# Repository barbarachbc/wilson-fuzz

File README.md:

# wilson-fuzz
Wilson Fuzz (a Fuzz Face clone)

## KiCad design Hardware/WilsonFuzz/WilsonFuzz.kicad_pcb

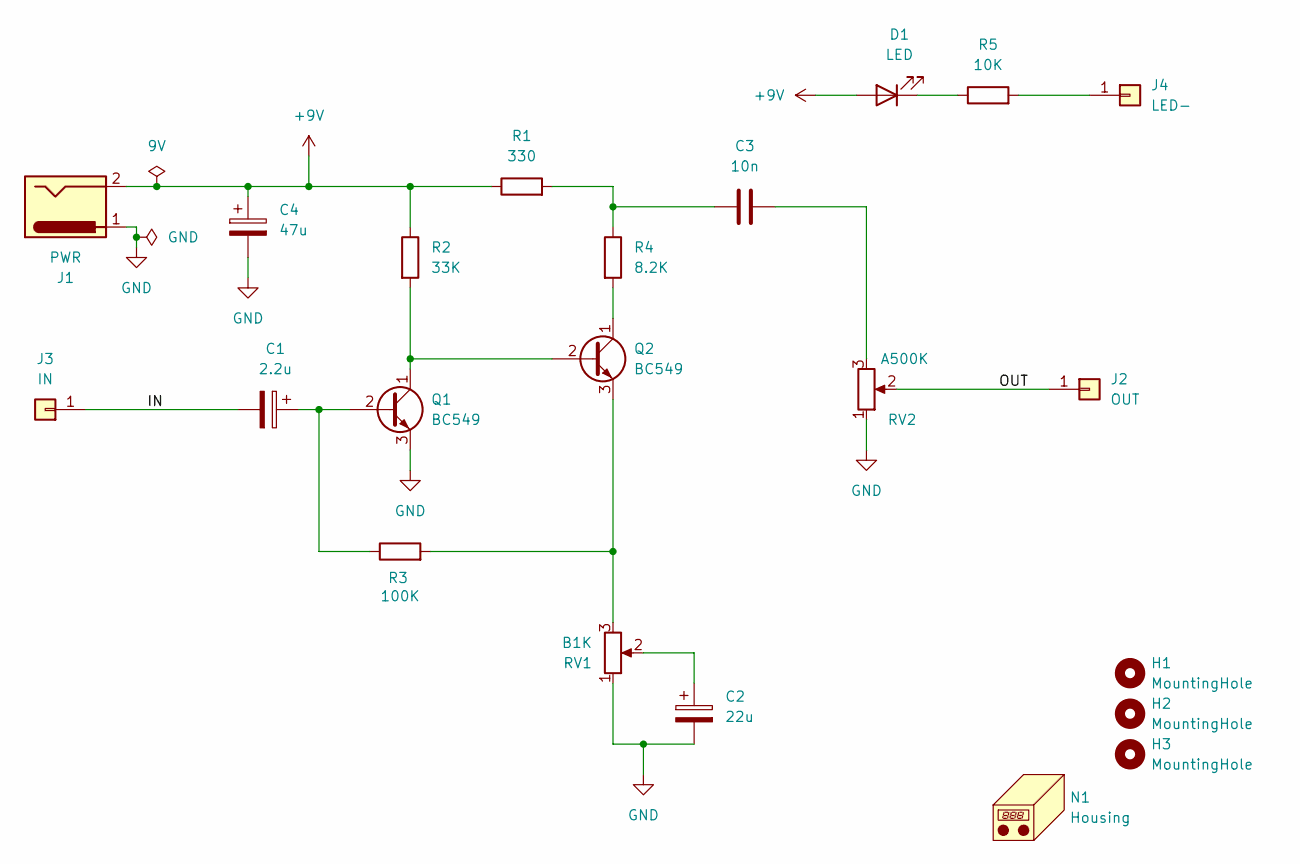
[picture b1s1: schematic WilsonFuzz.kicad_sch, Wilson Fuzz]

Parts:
C1: 2.2u; CP_Radial_D5.0mm_P2.00mm
C2: 22u; CP_Radial_D5.0mm_P2.00mm
C3: 10n; C_Rect_L7.2mm_W2.5mm_P5.00mm_FKS2_FKP2_MKS2_MKP2
C4: 47u; CP_Radial_D5.0mm_P2.00mm
D1: LED; LED_D3.0mm
H1, H2, H3: MountingHole; MountingHole_4mm
J1: PWR; PinHeader_1x02_P2.54mm_Vertical
J2: OUT; PinHeader_1x01_P2.54mm_Vertical
J3: IN; PinHeader_1x01_P2.54mm_Vertical
J4: LED-; PinHeader_1x01_P2.54mm_Vertical
N1: Housing; Barbarach_Smaller
Q1, Q2: BC549; TO-92_Inline_Wide
R1: 330; R_Axial_DIN0207_L6.3mm_D2.5mm_P7.62mm_Horizontal
R2: 33K; R_Axial_DIN0207_L6.3mm_D2.5mm_P7.62mm_Horizontal
R3: 100K; R_Axial_DIN0207_L6.3mm_D2.5mm_P7.62mm_Horizontal
R4: 8.2K; R_Axial_DIN0207_L6.3mm_D2.5mm_P7.62mm_Horizontal
R5: 10K; R_Axial_DIN0207_L6.3mm_D2.5mm_P7.62mm_Horizontal
RV1: B1K; PDB181K420K102B
RV2: A500K; PDB181K420K102B

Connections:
+9V: C4.1, D1.2 (A), J1.2, R1.1, R2.1
/IN: C1.2, J3.1
/OUT: J2.1, RV2.2
GND: C2.2, C4.2, J1.1, Q1.3 (E), RV1.1, RV2.1
unnamed: C2.1, RV1.2
unnamed: C3.1, R1.2, R4.1
unnamed: C3.2, RV2.3
unnamed: D1.1 (K), R5.1
unnamed: J4.1, R5.2
unnamed: C1.1, Q1.2 (B), R3.1
unnamed: Q1.1 (C), Q2.2 (B), R2.2
unnamed: Q2.1 (C), R4.2
unnamed: Q2.3 (E), R3.2, RV1.3

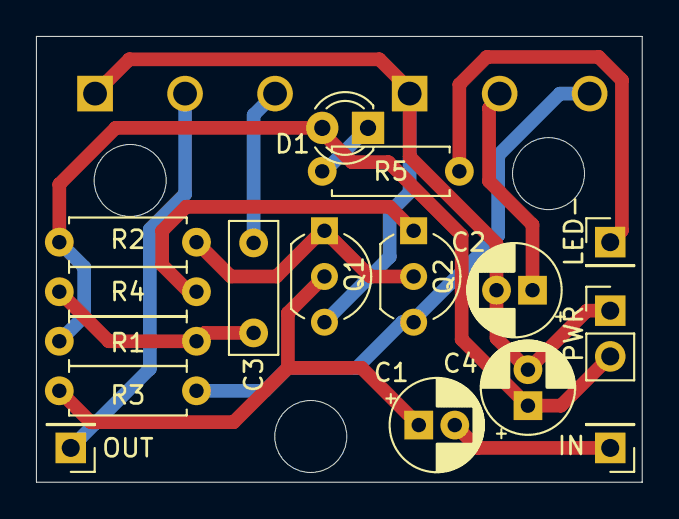
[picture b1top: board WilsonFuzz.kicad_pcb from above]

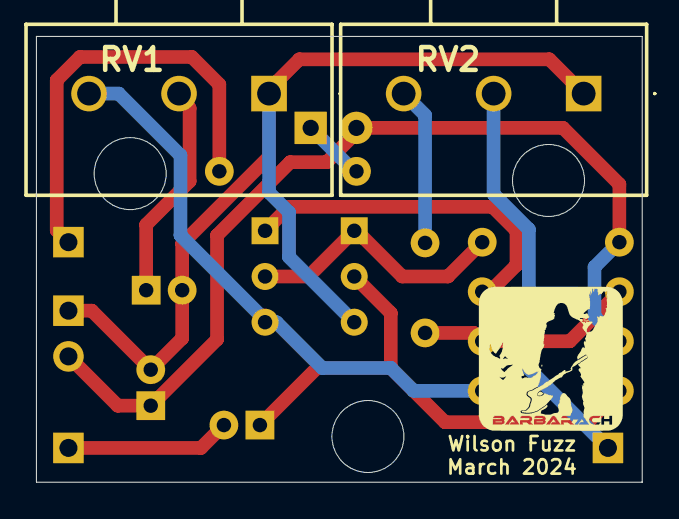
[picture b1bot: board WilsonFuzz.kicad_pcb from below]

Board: 2 copper layers, 33.7 x 24.8 mm, 22 parts (3 on the bottom side), 13 nets.

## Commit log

2024-04-04 Adding BOM. Fixing gitignore to exclude lck files
2024-05-29 Adding graphics and drilling planner
2024-05-30 Updated bom with different dc jack and knobs
2024-09-02 1590B enclosure drill template
